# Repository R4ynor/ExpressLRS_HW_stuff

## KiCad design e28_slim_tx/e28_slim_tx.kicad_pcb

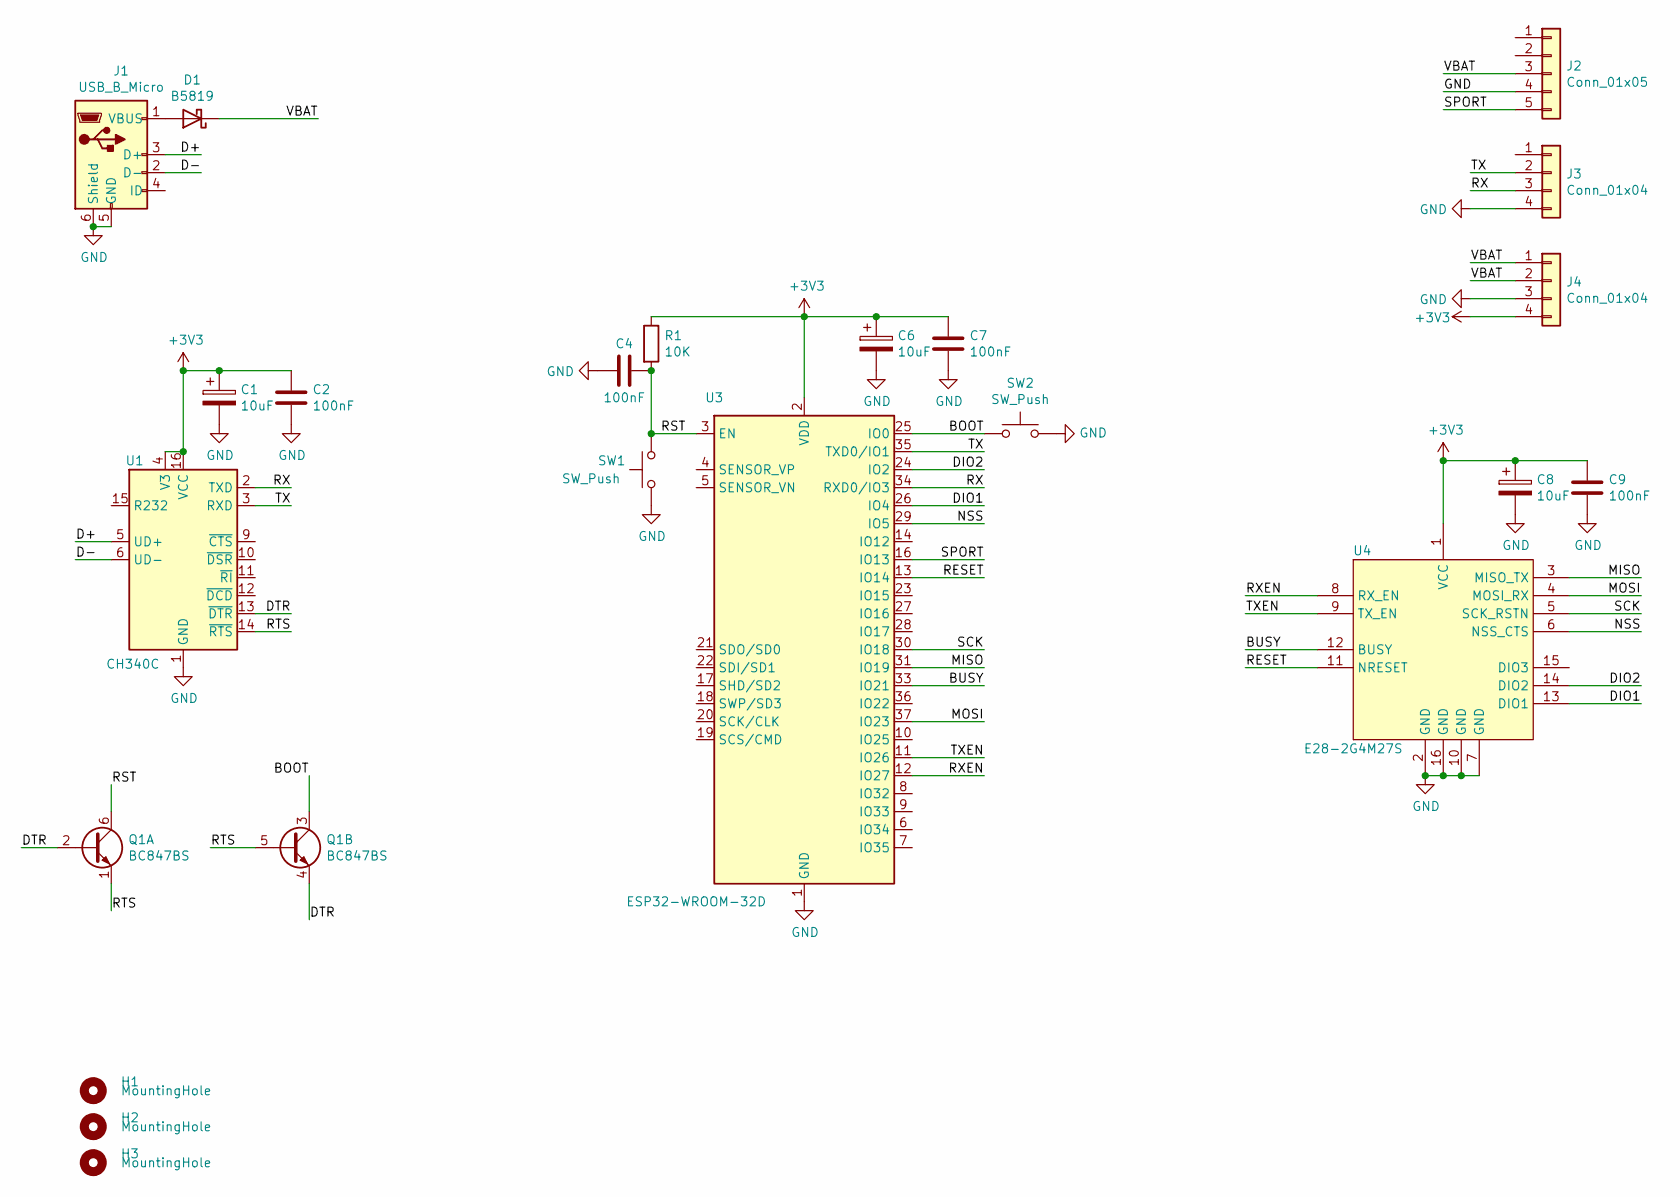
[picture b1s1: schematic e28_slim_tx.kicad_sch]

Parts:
C1, C6, C8: 10uF; CP_EIA-1608-08_AVX-J_Pad1.25x1.05mm_HandSolder
C2, C4, C7, C9: 100nF; C_0603_1608Metric_Pad1.05x0.95mm_HandSolder
D1: B5819; D_SOD-323_HandSoldering
H1, H2, H3: MountingHole; MountingHole_3.2mm_M3
J1: USB_B_Micro; USB_Micro-B_Wuerth_614105150721_Vertical
J2: Conn_01x05; MOLEX_0022142054
J3, J4: Conn_01x04; PinHeader_1x04_P2.54mm_Vertical
Q1: BC847BS; SOT-363_SC-70-6
R1: 10K; R_0603_1608Metric_Pad1.05x0.95mm_HandSolder
SW1, SW2: SW_Push; SW_SPST_TL3342
U1: CH340C; SOIC-16_3.9x9.9mm_P1.27mm
U3: ESP32-WROOM-32D; ESP32-WROOM-32
U4: E28-2G4M27S

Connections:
+3V3: C1.1, C2.1, C6.1, C7.1, C8.1, C9.1, J4.4, R1.1, U1.4 (V3), U1.16 (VCC), U3.2 (VDD), U4.1 (VCC)
/BOOT: Q1.3 (C2), SW2.1, U3.25 (IO0)
/BUSY: U3.33 (IO21), U4.12 (BUSY)
/D+: J1.3 (D+), U1.5 (UD+)
/D-: J1.2 (D-), U1.6 (UD-)
/DIO1: U3.26 (IO4), U4.13 (DIO1)
/DIO2: U3.24 (IO2), U4.14 (DIO2)
/DTR: Q1.2 (B1), Q1.4 (E2), U1.13 (~DTR)
/MISO: U3.31 (IO19), U4.3 (MISO_TX)
/MOSI: U3.37 (IO23), U4.4 (MOSI_RX)
/NSS: U3.29 (IO5), U4.6 (NSS_CTS)
/RESET: U3.13 (IO14), U4.11 (NRESET)
/RST: C4.2, Q1.6 (C1), R1.2, SW1.2, U3.3 (EN)
/RTS: Q1.1 (E1), Q1.5 (B2), U1.14 (~RTS)
/RX: J3.3, U1.2 (TXD), U3.34 (RXD0/IO3)
/RXEN: U3.12 (IO27), U4.8 (RX_EN)
/SCK: U3.30 (IO18), U4.5 (SCK_RSTN)
/SPORT: J2.5, U3.16 (IO13)
/TX: J3.2, U1.3 (RXD), U3.35 (TXD0/IO1)
/TXEN: U3.11 (IO26), U4.9 (TX_EN)
/VBAT: D1.1 (K), J2.3, J4.1, J4.2
GND: C1.2, C2.2, C4.1, C6.2, C7.2, C8.2, C9.2, J1.5 (GND), J1.6 (Shield), J2.4, J3.4, J4.3, SW1.1, SW2.2, U1.1 (GND), U3.1 (GND), U3.15 (GND), U3.38 (GND), U3.39 (GND), U4.2 (GND), U4.7 (GND), U4.10 (GND), U4.16 (GND)
unnamed: D1.2 (A), J1.1 (VBUS)

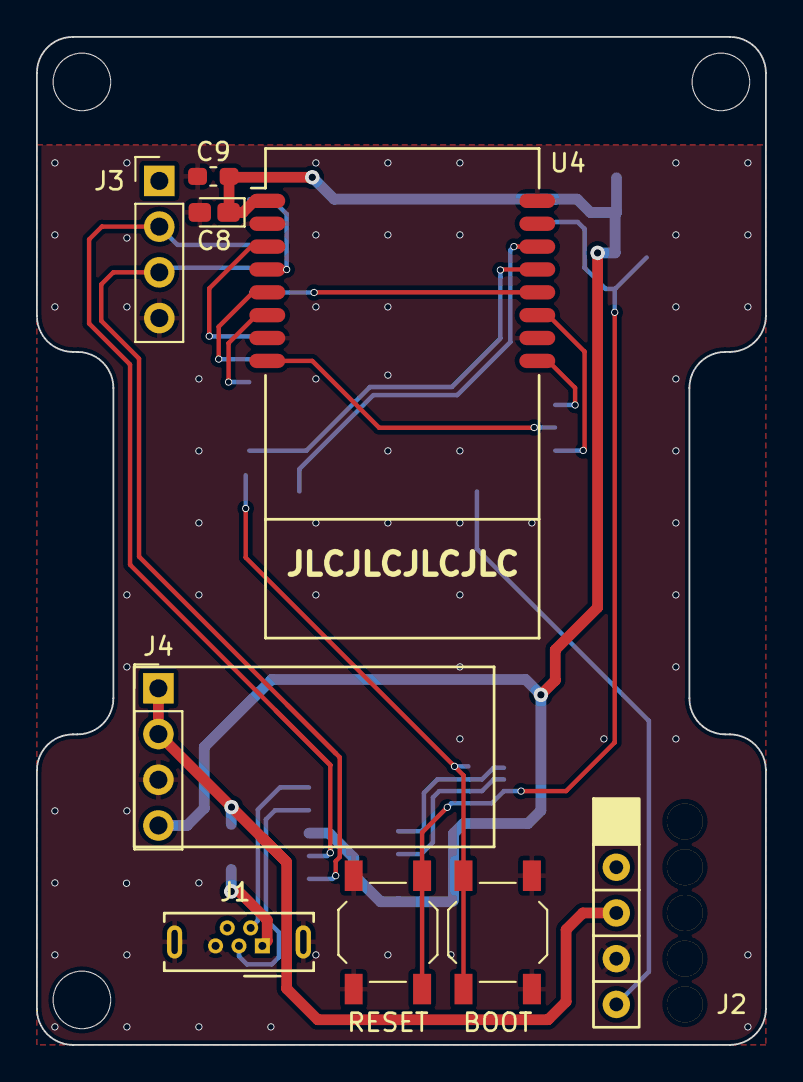
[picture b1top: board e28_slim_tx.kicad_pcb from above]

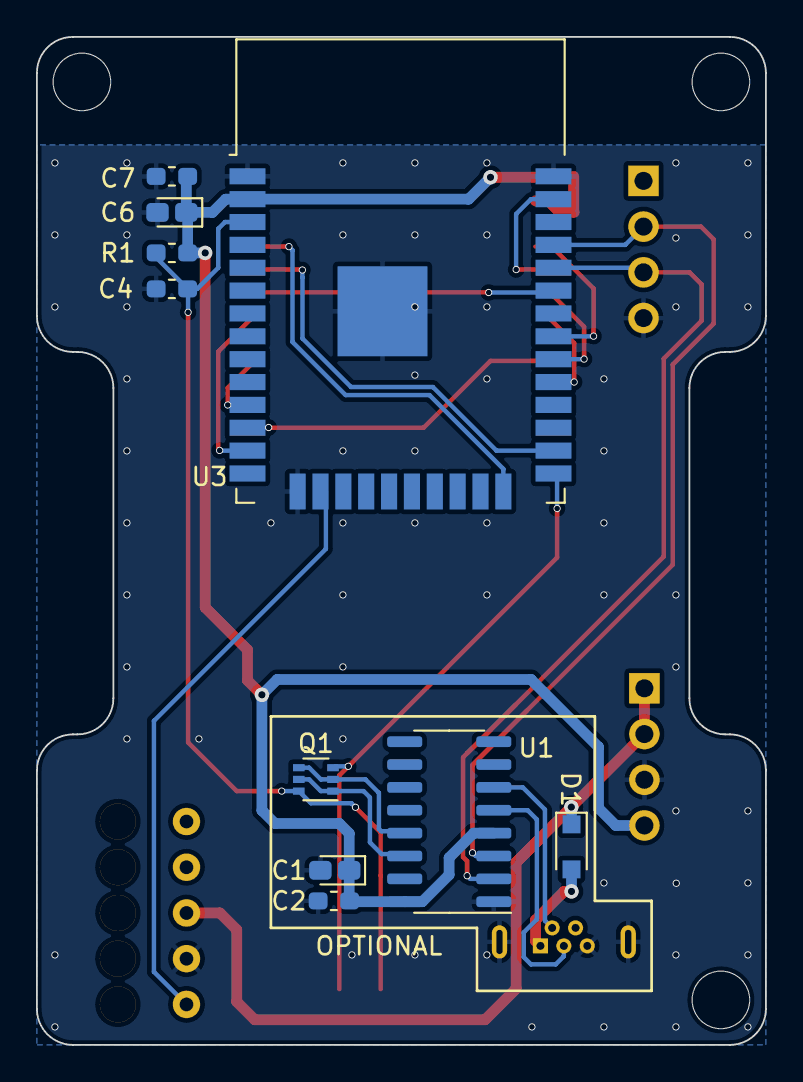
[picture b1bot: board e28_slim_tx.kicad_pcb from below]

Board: 2 copper layers, 40.5 x 56.0 mm, 22 parts (10 on the bottom side), 23 nets.

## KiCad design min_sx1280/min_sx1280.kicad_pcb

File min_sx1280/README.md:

# Mini 2.4GHz RX
This is a sx1280 receiver intended to be easier to solder with only an iron.

## BOM
https://docs.google.com/spreadsheets/d/1p7ZbwzJ3oUK5TnewW_nvrkTnwwBvXO2xWFpPxcCNbLk/edit?usp=sharing

## Build tip
Solder C3, C5 and R3 before the ESP-01F.

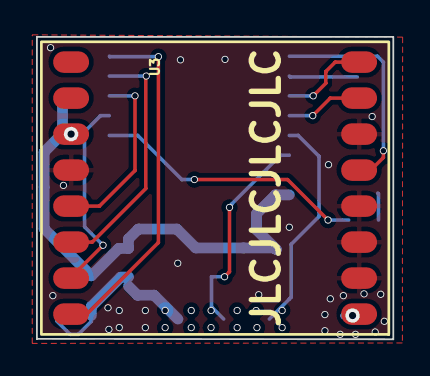
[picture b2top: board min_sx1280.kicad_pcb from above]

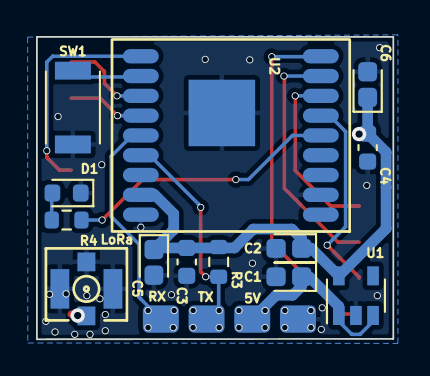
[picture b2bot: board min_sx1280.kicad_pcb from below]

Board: 2 copper layers, 19.8 x 16.8 mm, 15 parts (14 on the bottom side), 16 nets.

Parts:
AE2: Antenna_Shield; U.FL
C1, C2, C5, C6: CP; CP_EIA-1608-08_AVX-J
C3, C4: C; C_0603_1608Metric
D1: LED; LED_0603_1608Metric
J1: Conn_01x04; com_pads
R3, R4: 330; R_0603_1608Metric
SW1: SW_SPST; SW_3x4x2
U1: ME6211C33; SOT-23-5
U2: ESP-01F
U3: LoRa1280

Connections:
+3V3: C2.1, C3.1, C4.1, C5.1, C6.1, R3.1, U1.5 (OUT), U2.17 (3V3), U3.3 (VCC)
+5V: C1.1, J1.3, U1.1 (IN), U1.3 (EN)
/BOOT: SW1.1 (A), U2.11 (IO0)
/BUSY: U2.13 (IO5), U3.15 (BUSY)
/DIO1: U2.12 (IO4), U3.16 (DIO1)
/IO16: R4.1, U2.5 (IO16)
/MISO: U2.7 (IO12), U3.5 (MISO)
/MOSI: U2.8 (IO13), U3.6 (MOSI)
/NRESET: U2.10 (IO2), U3.13 (NRESET)
/NSS: U2.9 (IO15), U3.8 (NSS)
/RX: J1.1, U2.14 (RX)
/SCK: U2.6 (IO14), U3.7 (SCK)
/TX: J1.2, R3.2, U2.15 (TX)
GND: AE2.2 (Shield), C1.2, C2.2, C3.2, C4.2, C5.2, C6.2, D1.1 (K), J1.4, SW1.2 (B), U1.2 (GND), U2.2 (GND), U2.18 (GND), U2.19 (GND), U3.4 (GND), U3.10 (GND), U3.11 (GND), U3.12 (GND), U3.14 (GND)
unnamed: AE2.1 (A), U3.9 (ANT)
unnamed: D1.2 (A), R4.2

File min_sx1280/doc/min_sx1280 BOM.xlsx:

Reference | Quantity | Value | Description | Link
AE2 | 1.0 | Antenna_Shield | U.FL connector | https://lcsc.com/product-detail/RF-Connectors-Coaxial-Connec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
C1 C2 | 2.0 | 1uF | Ceramic capacitor 0603 | https://lcsc.com/product-detail/Multilayer-Ceramic-Capacitor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
C3 C4 | 2.0 | 100nF | Ceramic capacitor 0603 | https://lcsc.com/product-detail/Multilayer-Ceramic-Capacitor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
C5 C6 | 2.0 | 10uF | Tantalum capacitor | https://lcsc.com/product-detail/Tantalum-Capacitors_ROHM-Sem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
D1 | 1.0 | LED | Led 0603 | https://lcsc.com/product-detail/Light-Emitting-Diodes-LED_Or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
R3 R4 | 2.0 | 330.0 | Resistor 0603 | https://lcsc.com/product-detail/Chip-Resistor-Surface-Mount_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
SW1 | 1.0 | SW_SPST | Swtich | https://www.aliexpress.com/item/32855171871.html?spm=a2g0s.9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
U1 | 1.0 | ME6211C33 | 3v3 ldo sot23-5 | https://lcsc.com/product-detail/Dropout-Regulators-LDO_MICRO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
U2 | 1.0 | ESP-01F | esp-01f module | https://www.aliexpress.com/item/4000903500651.html?spm=a2g0s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
U3 | 1.0 | LoRa1280 | Gnice 1280 module | https://www.aliexpress.com/item/32946774361.html?spm=a2g0s.9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

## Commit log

2020-08-25 Sync
2020-08-26 Added some happy components
2020-08-31 Finished TX and RX, added 3d models
2020-09-03 Updated gitignore
2020-09-03 .gitignore fix
2020-10-28 Added minimal RX
2020-10-29 Minimal RX ready to route
2020-10-30 Min RX routing done
2020-11-05 Last tweaks and gerber files to min_sx1280 and e28_tx
2020-11-19 Fixed min button and added some pictures of the boards
2020-11-19 Ploted new gerbers
2020-11-21 Added schematics
2020-11-23 Added anti-ripping vias, generated new gerbers and added some documentation.
2021-01-09 Fixed USB psotion on e28_tx, populated e28_slim_tx project.
2021-06-19 added some symbols
